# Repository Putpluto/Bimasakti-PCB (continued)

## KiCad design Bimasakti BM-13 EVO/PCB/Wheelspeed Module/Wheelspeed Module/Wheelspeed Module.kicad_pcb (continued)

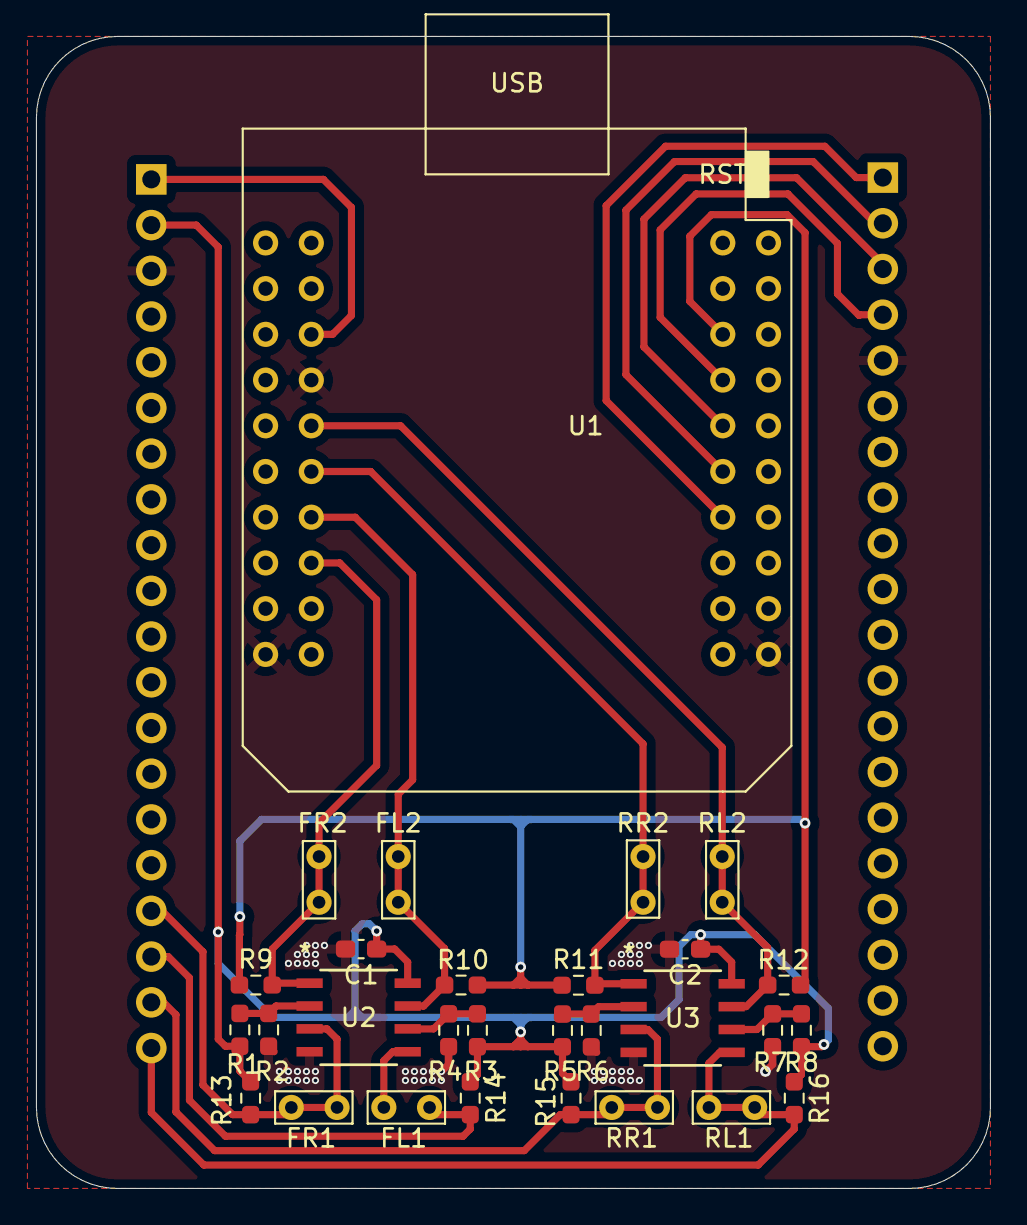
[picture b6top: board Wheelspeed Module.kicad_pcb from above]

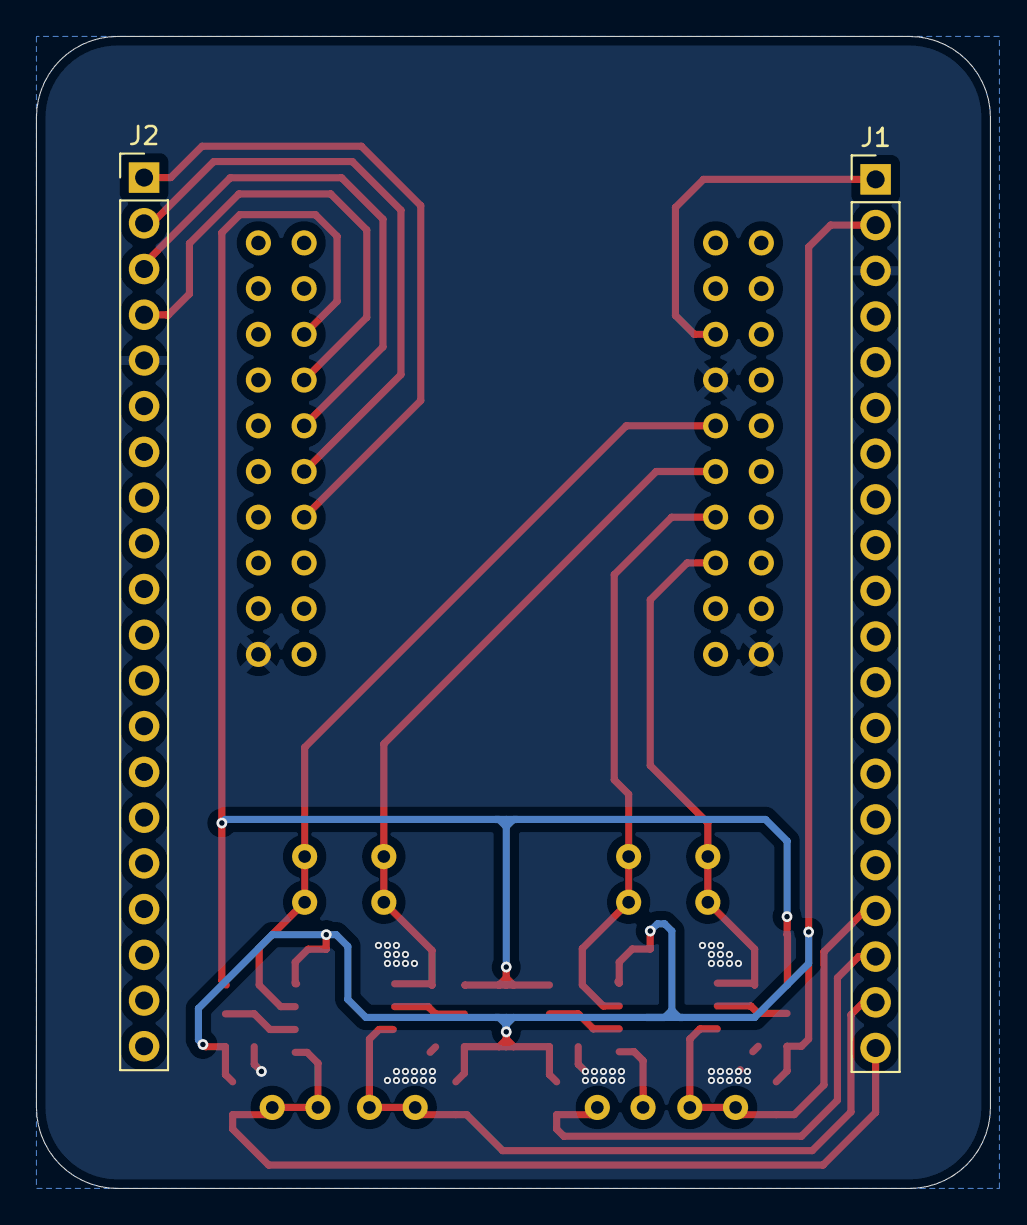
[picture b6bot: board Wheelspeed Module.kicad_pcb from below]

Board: 2 copper layers, 53.0 x 64.0 mm, 31 parts (2 on the bottom side), 20 nets.

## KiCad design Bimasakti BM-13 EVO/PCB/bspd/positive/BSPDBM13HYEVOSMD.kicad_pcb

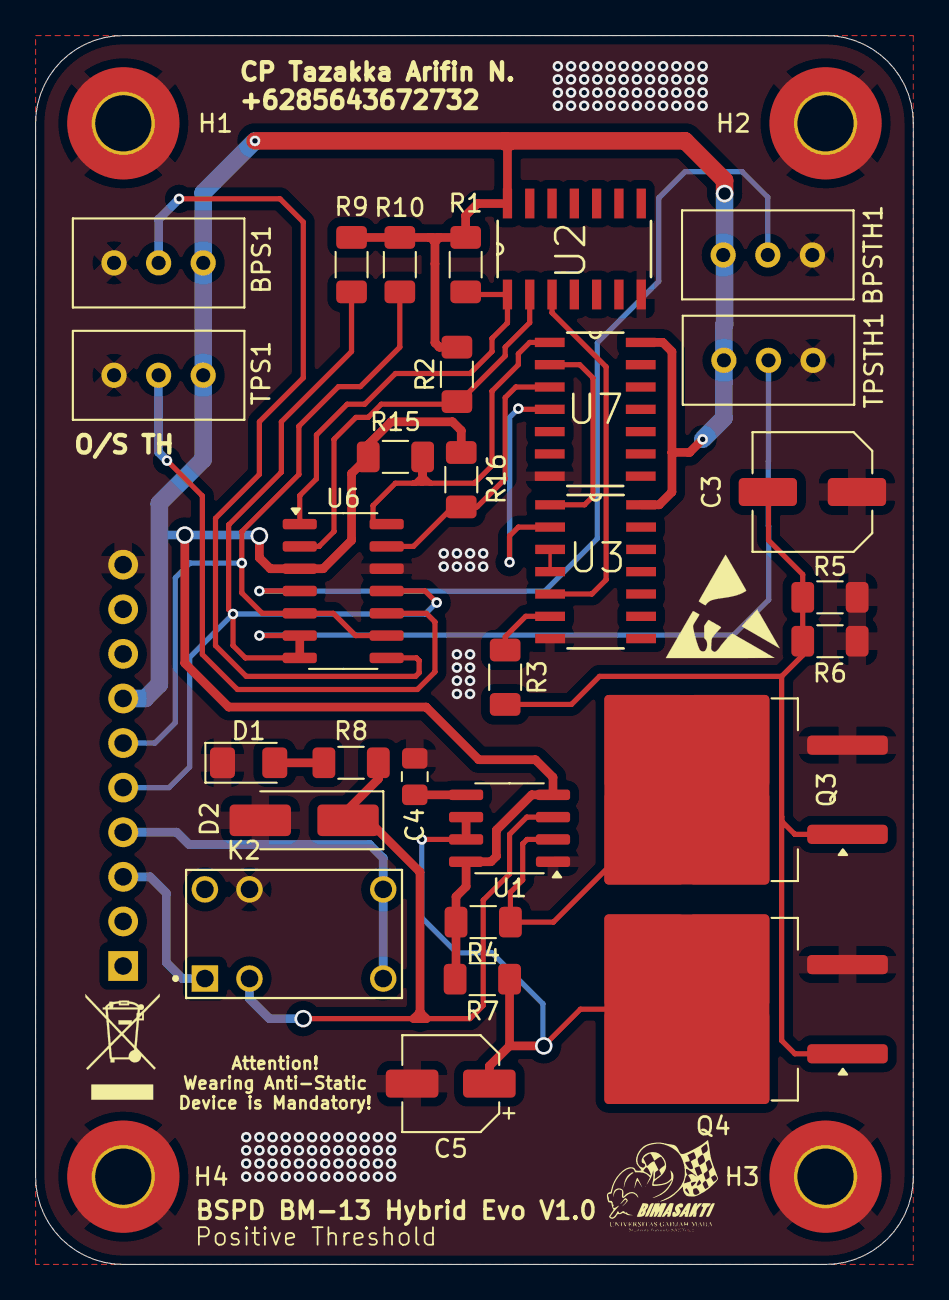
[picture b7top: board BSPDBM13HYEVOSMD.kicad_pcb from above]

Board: 2 copper layers, 50.0 x 70.0 mm, 34 parts (1 on the bottom side), 24 nets.

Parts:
BPS1: R_Potentiometer_Trim; Potentiometer_Bourns_3296W_Vertical
BPSTH1: R_Potentiometer_Trim; Potentiometer_Bourns_3296W_Vertical
C3: 100uF; C_Elec_6.3x7.7
C4: 1uF; C_0805_2012Metric_Pad1.18x1.45mm_HandSolder
C5: 10uF; CP_Elec_5x5.3
D1: LED; LED_1206_3216Metric_Pad1.42x1.75mm_HandSolder
D2: SS210; D_SMA_Handsoldering
H1, H2, H3, H4: MountingHole_Pad; MountingHole_3.2mm_M3_Pad_TopBottom
J1: Conn_01x10_Pin; PinHeader_1x10_P2.54mm_Vertical
K2: G5V-1_DC5; RELAY_G5V-1_DC5
Q3, Q4: IRFS4127; TO-263-2
R1, R2, R3, R4, R15, R16: 10K; R_1206_3216Metric_Pad1.30x1.75mm_HandSolder
R5, R6: 100K; R_1206_3216Metric_Pad1.30x1.75mm_HandSolder
R7, R9, R10: 1M; R_1206_3216Metric_Pad1.30x1.75mm_HandSolder
R8: 150; R_1206_3216Metric_Pad1.30x1.75mm_HandSolder
TPS1: R_Potentiometer_Trim; Potentiometer_Bourns_3296W_Vertical
TPSTH1: R_Potentiometer_Trim; Potentiometer_Bourns_3296W_Vertical
U1: NE555D; SOIC-8_3.9x4.9mm_P1.27mm
U2: 74HC08D-T; SOIC127P600X175-14N
U3: 74HC32D_653; SOIC127P600X175-14N
U6: LM339; SOIC-14_3.9x8.7mm_P1.27mm
U7: 74HC04D; SOIC127P600X175-14N

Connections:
+5V: BPS1.1, BPSTH1.1, J1.7, R1.1, R2.2, R4.2, R7.2, R9.1, R10.1, R15.1, R16.1, TPS1.1, TPSTH1.1, U1.4 (R), U1.8 (VCC), U2.14 (VCC), U3.14 (VCC), U6.3 (V+), U7.14 (VCC)
BrakePress: J1.6, R10.2, U6.5 (+), U6.9 (+)
COM: J1.4, K2.5, K2.6
GND: BPS1.3, BPSTH1.3, C3.1, C4.2, C5.2, D1.1 (K), D2.2 (A), H1.1, H2.1, H3.1, H4.1, J1.10, K2.9, Q3.3 (S), Q4.3 (S), R5.1, R6.1, TPS1.3, TPSTH1.3, U1.1 (GND), U2.7 (GND), U3.7 (GND), U6.12 (V-), U7.7 (GND)
NC: J1.3, K2.1
unnamed: D1.2 (A), R8.1
unnamed: D2.1 (K), K2.2, R8.2, U1.3 (Q)
unnamed: Q3.2 (D), R4.1, U1.2 (TR)
unnamed: C3.2, Q3.1 (G), Q4.1 (G), R3.2, R5.2, R6.2
unnamed: C5.1, Q4.2 (D), R7.1, U1.6 (THR), U1.7 (DIS)
unnamed: C4.1, U1.5 (CV)
unnamed: R1.2, U2.1 (1A), U6.1
unnamed: R2.1, U2.2 (1B), U6.2
unnamed: U2.3 (1Y), U3.5 (2B)
unnamed: U3.1 (1A), U7.2 (1Y)
unnamed: U3.2 (1B), U7.4 (2Y)
unnamed: U3.3 (1Y), U3.4 (2A)
unnamed: R3.1, U3.6 (2Y)
unnamed: BPSTH1.2, U6.4 (-)
unnamed: TPS1.2, U6.10 (-)
unnamed: BPS1.2, U6.8 (-)
unnamed: R15.2, U6.14, U7.1 (1A)
unnamed: R16.2, U6.13, U7.3 (2A)
ThrottlePos: J1.5, R9.2, TPSTH1.2, U6.6 (-), U6.7 (+), U6.11 (+)

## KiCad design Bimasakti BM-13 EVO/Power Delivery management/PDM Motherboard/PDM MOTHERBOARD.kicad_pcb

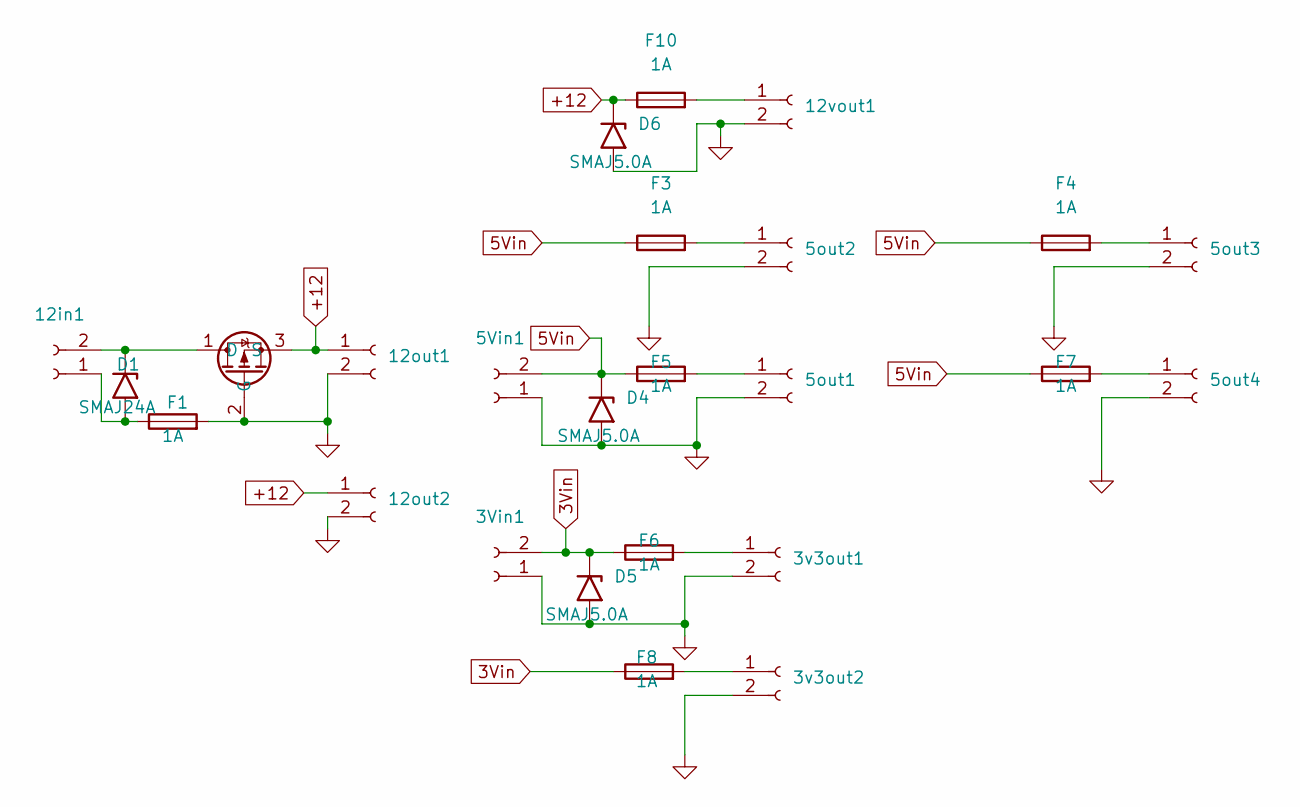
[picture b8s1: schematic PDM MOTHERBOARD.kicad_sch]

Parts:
3Vin1, 3v3out1, 3v3out2, 5Vin1, 5out1, 5out2, 5out3, 5out4, 12in1, 12out1, 12out2, 12vout1: JST_EH_B2B-EH-A_1x02_P2.50mm_Vertical
D1: SMAJ24A; D_SMA
D4, D5, D6: SMAJ5.0A; D_SMA
F1, F3, F4, F5, F6, F7, F8, F10: 1A; Fuseholder_Cylinder-5x20mm_Schurter_0031_8201_Horizontal_Op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
U1: SOIC-8 (AOD)

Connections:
3Vin: 3Vin1.2, D5.1 (A1), F6.1, F8.1
5Vin: 5Vin1.2, D4.1 (A1), F3.1, F4.1, F5.1, F7.1
+12: 12out1.1, 12out2.1, D6.1 (A1), F10.1, U1.3 (S)
GND: 3Vin1.1, 3v3out1.2, 3v3out2.2, 5Vin1.1, 5out1.2, 5out2.2, 5out3.2, 5out4.2, 12out1.2, 12out2.2, 12vout1.2, D4.2 (A2), D5.2 (A2), D6.2 (A2), F1.2, U1.2 (G)
unnamed: 3v3out1.1, F6.2
unnamed: 3v3out2.1, F8.2
unnamed: 5out1.1, F5.2
unnamed: 5out2.1, F3.2
unnamed: 5out3.1, F4.2
unnamed: 5out4.1, F7.2
unnamed: 12in1.1, D1.2 (A2), F1.1
unnamed: 12in1.2, D1.1 (A1), U1.1 (D)
unnamed: 12vout1.1, F10.2

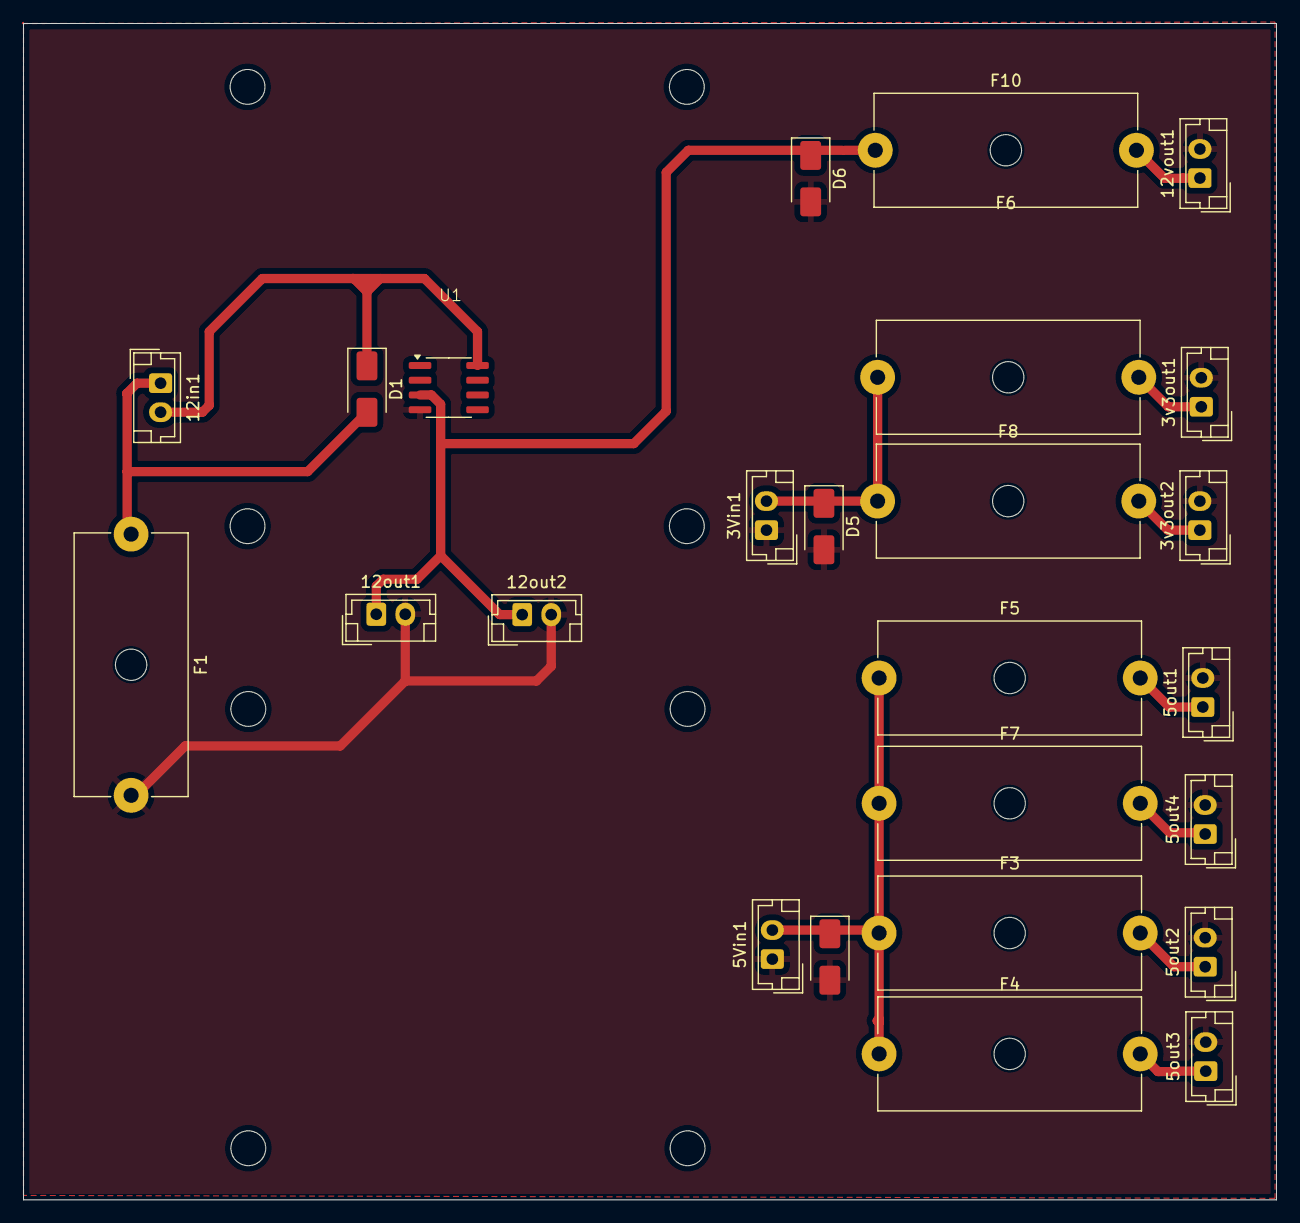
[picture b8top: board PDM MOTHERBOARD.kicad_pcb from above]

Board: 2 copper layers, 108.0 x 101.3 mm, 25 parts (0 on the bottom side), 13 nets.
